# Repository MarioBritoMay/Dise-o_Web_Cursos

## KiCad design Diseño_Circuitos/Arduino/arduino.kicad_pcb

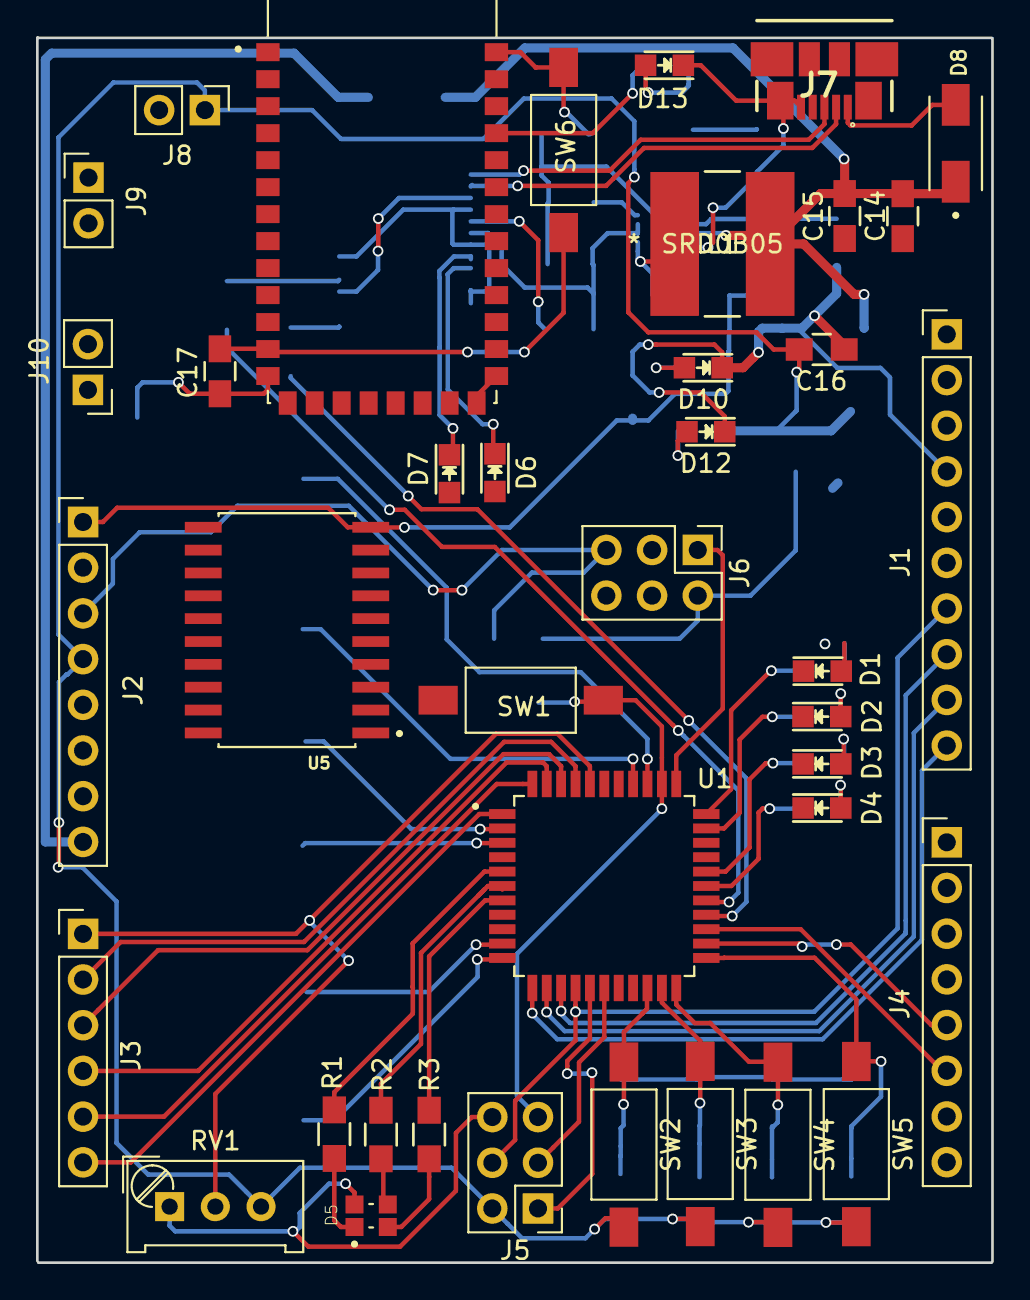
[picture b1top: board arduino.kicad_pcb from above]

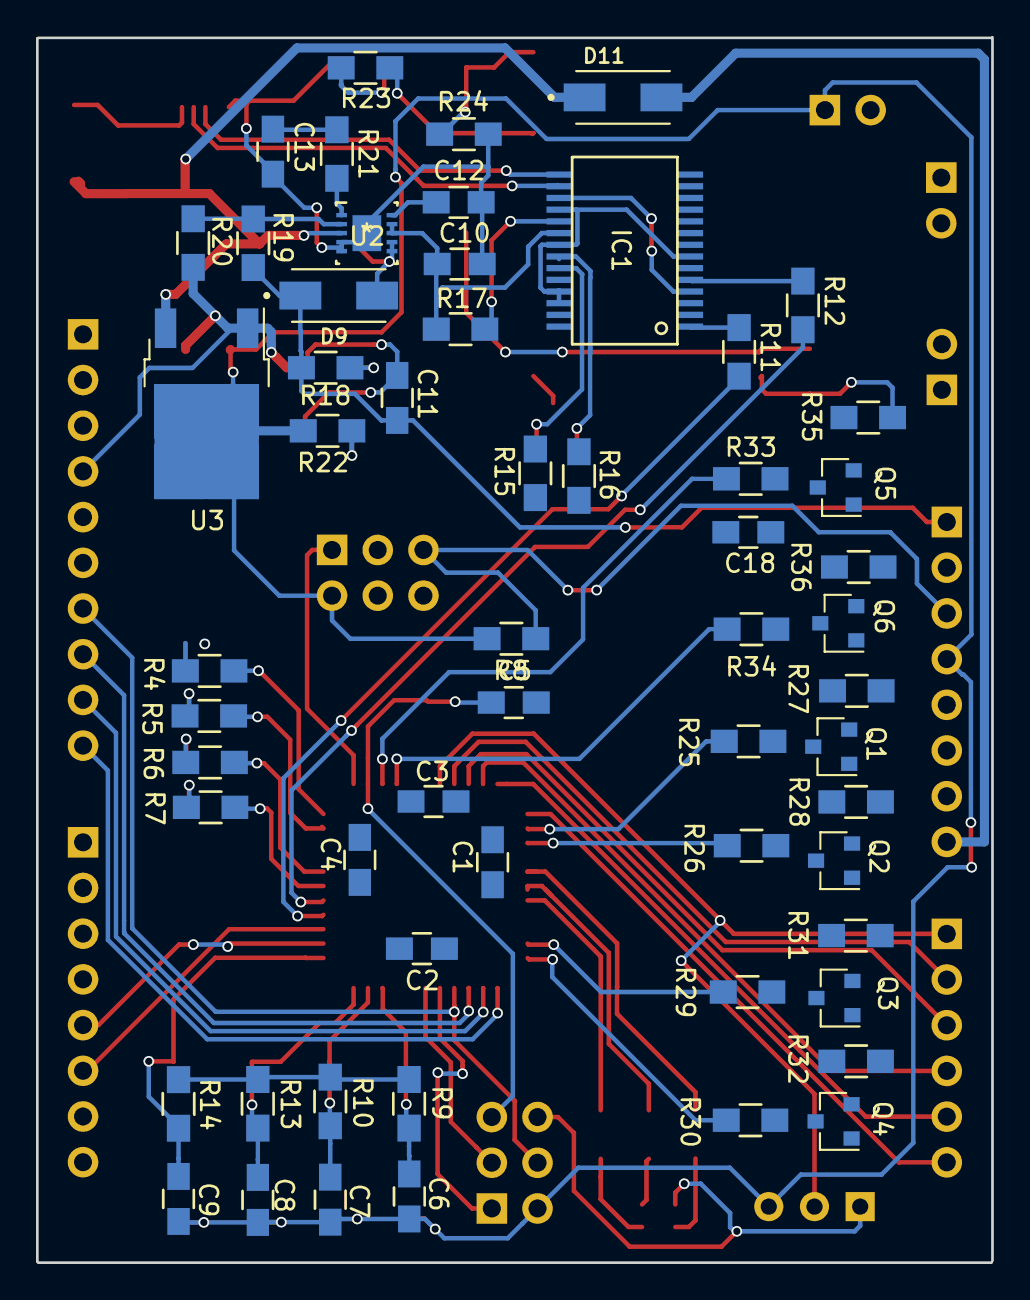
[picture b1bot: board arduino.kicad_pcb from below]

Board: 2 copper layers, 53.1 x 68.1 mm, 97 parts (58 on the bottom side), 86 nets.

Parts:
C1, C2, C3, C4, C5, C6, C7, C8, C9, C10, C17: 100nF; C_0805_HandSoldering
C11: 22uf; C_0805_HandSoldering
C12, C18: 100nf; C_0805_HandSoldering
C13: 820pf; C_0805_HandSoldering
C14: 1uf; C_0805_HandSoldering
C15, C16: 10uf; C_0805_HandSoldering
D1, D2, D6, D7: AP2012HD; LED_0805
D3, D4: LTW-170TK; LED_0805
D5: LED_RCGB; LED_150080M153000
D8, D9, D11: B340A-13-F; DIOM5226X240N
D10, D12, D13: LED_ALT; LED_0805
IC1: FT232RL; SSOP28-LD
J1: Conn_01x10; Pin_Header_Straight_1x10_Pitch2.54mm
J2, J4: Conn_01x08; Pin_Header_Straight_1x08_Pitch2.54mm
J3: Conn_01x06; Pin_Header_Straight_1x06_Pitch2.54mm
J5, J6: Conn_02x03_Counter_Clockwise; Pin_Header_Straight_2x03_Pitch2.54mm
J7: USB_OTG; 47346-0001
J8, J9, J10: Conn_01x02; Pin_Header_Straight_1x02_Pitch2.54mm
L1: SRD0B05; SDR0805-332KL
Q1, Q2, Q3, Q4, Q5, Q6: MMBT3904; SOT-23
R1, R2, R3, R4, R5, R6, R7, R15, R16, R18, R22: 330; R_0805_HandSoldering
R8, R9, R10, R13, R14, R17, R27, R28, R31, R32, R35, R36: 10K; R_0805_HandSoldering
R11, R12, R25, R26, R29, R30, R33, R34: 1K; R_0805_HandSoldering
R19: 232K; R_0805_HandSoldering
R20: 26K; R_0805_HandSoldering
R21: 105K; R_0805_HandSoldering
R23: 2k; R_0805_HandSoldering
R24: 10k; R_0805_HandSoldering
RV1: POT_TRIM; Potentiometer_Trimmer_Bourns_PV36W
SW1, SW2, SW3, SW4, SW5, SW6: SW_Push; SW_SPST_FSMSM
U1: ATXMEGA32A4U-AU
U2: TPS61087DSCR
U3: LM1117-3.3; TO-252-2
U4: HC-05; XCVR_HC-05
U5: L293DD; SOIC127P1032X265-20N

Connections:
+3.3VP: C17.1, J8.2, SW6.2, U4.12
+3V3: C1.1, C2.1, C3.1, C4.1, C6.1, C7.1, C8.1, C9.1, C16.1, J2.4, J5.2, J6.2, J8.1, R8.1, R22.1, RV1.3, SW2.2, SW3.2, SW4.2, SW5.2, U1.9, U1.19, U1.31, U1.39, U3.2
+5V: C10.1, C14.1, C15.1, C18.1, D8.C, D11.C, IC1.20, J2.5, L1.2, Q1.3, Q2.3, Q3.3, Q4.3, Q5.3, Q6.3, R15.1, R16.1, R17.1, U2.3, U2.8, U2.9, U3.3, U5.20
+12V: C11.1, D9.C, J2.1, R18.1, R19.1, U5.10
/A0: J3.1, RV1.2, U1.40
/A1: J3.2, U1.41
/A2: J3.3, U1.42
/A3: J3.4, U1.43
/A4: J3.5, U1.44
/A5: J3.6, U1.1
/AREF: J1.3, U1.4
/BTN1: C6.2, J4.1, R9.2, SW2.1, U1.20
/BTN2: C7.2, J4.2, R10.2, SW3.1, U1.21
/BTN3: C8.2, J4.3, R13.2, SW4.1, U1.22
/BTN4: C9.2, J4.4, R14.2, SW5.1, U1.23
/Driver_Motors/EN_1: Q3.2, R31.1, U5.1
/Driver_Motors/EN_2: Q4.2, R32.1, U5.11
/Driver_Motors/INPUT_1: Q1.2, R27.1, U5.2
/Driver_Motors/INPUT_2: Q2.2, R28.1, U5.9
/Driver_Motors/INPUT_3: Q5.2, R35.1, U5.12
/Driver_Motors/INPUT_4: Q6.2, R36.1, U5.19
/LED1: J1.2, R7.2, U1.28
/LED2: J1.1, R6.2, U1.29
/LED_B: R3.2, U1.7
/LED_G: R2.2, U1.6
/LED_R: R1.2, U1.5
/MISO: J1.6, J5.1, U1.16
/MOSI: J1.7, J5.4, U1.15
/PD4: J4.5, U1.24
/PD5: J4.6, U1.25
/PDI_DATA: J6.1, U1.34
/PWM: J1.9, U1.13
/PWM/CS: J1.8, U1.14
/RESET: C5.1, J2.3, J5.5, J6.5, R8.2, SW1.2, U1.35
/RXD: IC1.5, R12.2
/RXD1: J4.8, R11.2, U1.26
/RXLED: D7.1, IC1.22
/SCK: J1.5, J5.3, U1.17
/TXD: IC1.1, R11.1
/TXD1: J4.7, R12.1, U1.27
/TXLED: D6.1, IC1.23
BT_RX: R4.2, U1.33, U4.2
BT_STATE: J1.10, U1.12, U4.32
BT_TX: R5.2, U1.32, U4.1
D+: IC1.15, J7.3
D-: IC1.16, J7.2
GND: C1.2, C2.2, C3.2, C4.2, C5.2, C10.2, C11.2, C12.2, C13.2, C14.2, C15.2, C16.2, C17.2, C18.2, D1.1, D2.1, D3.1, D4.1, D5.2, D10.1, D12.1, D13.1, IC1.7, IC1.18, IC1.21, IC1.25, IC1.26, J1.4, J2.6, J2.7, J5.6, J6.6, J7.5, J7.6, R9.1, R10.1, R13.1, R14.1, R20.2, R24.2, R27.2, R28.2, R31.2, R32.2, R35.2, R36.2, RV1.1, SW1.1, U1.8, U1.18, U1.30, U1.38, U2.4, U2.5, U2.11, U3.1, U4.13, U4.21, U4.22, U5.4, U5.5, U5.6, U5.7, U5.14, U5.15, U5.16, U5.17
MOT1_A: R25.2, U1.2
MOT1_B: R26.2, U1.3
MOT1_PWM: R29.2, U1.10
MOT2_A: R33.2, U1.36
MOT2_B: R34.2, U1.37
MOT2_PWM: R30.2, U1.11
unnamed: C12.1, U2.10
unnamed: C13.1, R21.2
unnamed: D1.2, R4.1
unnamed: D2.2, R5.1
unnamed: D3.2, R6.1
unnamed: D4.2, R7.1
unnamed: D5.1, R1.1
unnamed: D5.3, R2.1
unnamed: D5.4, R3.1
unnamed: D6.2, R15.2
unnamed: D7.2, R16.2
unnamed: D8.A, J7.1
unnamed: D9.A, L1.1, U2.6, U2.7
unnamed: D10.2, R18.2
unnamed: D12.2, R22.2
unnamed: D13.2, R23.2
unnamed: IC1.4, IC1.17
unnamed: IC1.19, R17.2
unnamed: J9.1, U5.3
unnamed: J9.2, U5.8
unnamed: J10.1, U5.13
unnamed: J10.2, U5.18
unnamed: Q1.1, R25.1
unnamed: Q2.1, R26.1
unnamed: Q3.1, R29.1
unnamed: Q4.1, R30.1
unnamed: Q5.1, R33.1
unnamed: Q6.1, R34.1
unnamed: R19.2, R20.1, U2.2
unnamed: R21.1, U2.1
unnamed: R23.1, U4.31
unnamed: R24.1, SW6.1, U4.34
VIN: D11.A, J2.8

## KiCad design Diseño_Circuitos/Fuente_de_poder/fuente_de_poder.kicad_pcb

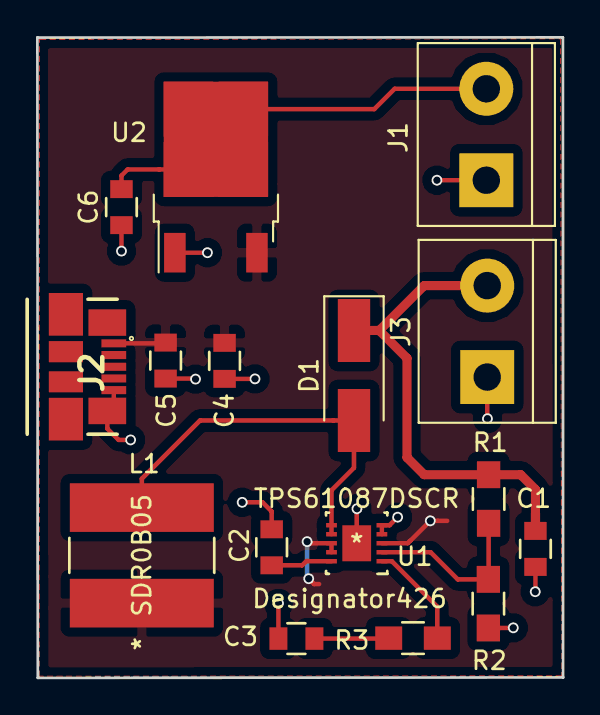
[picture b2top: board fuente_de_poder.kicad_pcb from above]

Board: 2 copper layers, 29.2 x 35.6 mm, 16 parts (0 on the bottom side), 9 nets.

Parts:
C1: 22uf; C_0805
C2: 100nf; C_0805
C3: 820pf; C_0805
C4, C6: 10uf; C_0805
C5: 1uf; C_0805
D1: B340A-113-F; D_SMA_Handsoldering
J1, J3: Conn_01x02; TerminalBlock_bornier-2_P5.08mm
J2: USB_OTG; 47346-0001
L1: SDR0B05; SDR0805-332KL
R1: 232k; R_0805_HandSoldering
R2: 26.7k; R_0805_HandSoldering
R3: 105k; R_0805_HandSoldering
U1: TPS61087DSCR
U2: LM1117-3.3; TO-252-2

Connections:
+3V3: C6.1, J1.2, U2.2
+5V: C4.1, C5.1, J2.1, L1.1, U1.3, U1.8, U1.9, U2.3
+12V: C1.1, D1.1, J3.2, R1.1
GND: C1.2, C2.2, C3.2, C4.2, C5.2, C6.2, J1.1, J2.5, J2.6, J3.1, R2.2, U1.4, U1.5, U1.11, U2.1
unnamed: C2.1, U1.10
unnamed: C3.1, R3.2
unnamed: D1.2, L1.2, U1.6, U1.7
unnamed: R1.2, R2.1, U1.2
unnamed: R3.1, U1.1

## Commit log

2020-08-13 cursos tomados añadidos
2020-08-17 carpeta de ejercicios añadida
2020-08-18 autoPlay & autopause added
2020-08-19 service Worker added
2020-08-24 typeScript added
2020-08-27 patrones de diseño
2020-09-07 introduction of c
2020-09-08 flujo C terminado
2020-09-18 pcb finished
2020-09-29 arduino dir added
2020-09-29 schematic 60%
2020-09-30 schematic completed
2020-10-05 pcb components placed
2020-10-06 power supply rutted
2020-10-06 pcb buttons and outputs traced

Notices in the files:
parts and their libraries:
Copyright 2016 Accelerated Designs. All rights reserved.
